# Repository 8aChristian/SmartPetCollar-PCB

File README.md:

# 🐾 SmartPet — Collar Inteligente para Mascotas (Smart Pet Collar PCB)

**SmartPet** es una solución de hardware embebido de grado industrial para collares inteligentes de mascotas (*pet wearables*). Diseñado en **KiCad 10**, integra procesamiento ultrarrápido con conectividad **Wi-Fi / Bluetooth Low Energy (BLE)**, posicionamiento satelital **GNSS/GPS con antena de parche integrada**, sensores de **actividad e inclinación triaxial (IMU)**, medición de **temperatura corporal (NTC)** y un sistema completo de **gestión de batería LiPo con recarga USB-C**.

---

## 📸 Vistas del Diseño de PCB

A continuación se presentan las vistas vectoriales de alta resolución del circuito impreso de 2 capas:

| Cara Superior (F.Cu & Serigrafía) | Cara Inferior (B.Cu & Ruteo 45°) |
| :---: | :---: |
|  |  |
| **Top Layer:** ESP32-C3, Módulo GPS, Cargador LiPo, IMU y Conectores | **Bottom Layer:** Sensor NTC, Pistas de Cruce y Plano GND de Retorno |

> 📄 **Documentación Gráfica y Planos de Fabricación:**
> - 🗺️ **Diagrama Esquemático Vectorial (SVG):** [`docs/SmartPet.svg`](docs/SmartPet.svg)
> - 📑 **Layout de PCB con Capas Combinadas (PDF):** [`docs/SmartPet_PCB_Layout.pdf`](docs/SmartPet_PCB_Layout.pdf)
> - 📦 **Paquete Completo de Gerbers RS-274X y Taladros Excellon:** [`fabrication/gerbers/`](fabrication/gerbers/)
> - 📐 **Reglas de Diseño Customizadas para Autorouter:** [`SmartPet.kicad_dru`](SmartPet.kicad_dru)

---

## ⚙️ Clases de Red y Reglas de Ruteo (NetClasses & Autorouter Rules)

El proyecto cuenta con **NetClasses jerárquicas preconfiguradas** según las normas **IPC-2152** e **IPC-2221** para garantizar un ruteo manual o automatizado (*Autorouter / Freerouting*) óptimo:

| Clase de Red (*NetClass*) | Redes Asignadas (*Nets*) | Ancho de Pista (*Width*) | Aislamiento (*Clearance*) | Vía (Diámetro / Taladro) | Función de Ingeniería |
| :--- | :--- | :--- | :--- | :--- | :--- |
| **`Power_Heavy`** | `VBUS`, `VBAT`, `GND` | **$0.80	ext{ mm}$** ($32	ext{ mil}$) | $0.35	ext{ mm}$ ($14	ext{ mil}$) | $arnothing 1.00	ext{ mm}$ / $0.50	ext{ mm}$ | Potencia principal de batería LiPo y bus USB-C (hasta 1.5A) |
| **`Power_Secondary`** | `+3.3V` | **$0.50	ext{ mm}$** ($20	ext{ mil}$) | $0.30	ext{ mm}$ ($12	ext{ mil}$) | $arnothing 0.80	ext{ mm}$ / $0.40	ext{ mm}$ | Riel regulado por LDO AP2112K para ESP32-C3 y sensores |
| **`Signals_Analog`** | `NTC_ADC`, `*ADC*` | **$0.35	ext{ mm}$** ($14	ext{ mil}$) | $0.25	ext{ mm}$ ($10	ext{ mil}$) | $arnothing 0.80	ext{ mm}$ / $0.40	ext{ mm}$ | Señal analógica de temperatura con filtro RC |
| **`Default` / `Digital`** | `I2C_*`, `GPS_*`, `ESP_*`, `USB_*`, `LED_*`, `LIS3DH_*` | **$0.25	ext{ mm}$** ($10	ext{ mil}$) | $0.20	ext{ mm}$ ($8	ext{ mil}$) | $arnothing 0.80	ext{ mm}$ / $0.40	ext{ mm}$ | Buses digitales de alta y media velocidad (I2C, UART, GPIOs) |

---

## 1. 🏗️ Arquitectura General del Sistema

```mermaid
graph TD
    subgraph ALIMENTACIÓN & GESTIÓN DE ENERGÍA
        USBC[Puerto USB-C 16P] -->|VBUS 5.0V| CHG[MCP73831T Cargador LiPo 4.2V]
        BATT[Batería LiPo 3.7V 350mAh] <-->|VBAT| CHG
        CHG -->|VBAT| LDO[AP2112K-3.3 CMOS Ultra-LDO 600mA]
        LDO -->|+3.3V Power Rail| VCC_BUS[Rail de Potencia 3.3V Limpio]
    end

    subgraph PROCESAMIENTO & COMUNICACIONES
        VCC_BUS --> MCU[ESP32-C3-WROOM-02-N4<br/>RISC-V 32-bit @ 160MHz]
        MCU -->|BLE Beacon 2.4GHz| BLE_PING[Rastreo Local Proximidad AirTag]
        MCU -->|Wi-Fi 802.11 b/g/n| CLOUD[Sincronización en el Hogar]
    end

    subgraph LOCALIZACIÓN SATELITAL
        VCC_BUS --> GPS[u-blox SAM-M8Q GNSS<br/>Antena de Parche Integrada]
        GPS -->|UART NMEA TX/RX @ 9600-115200| MCU
        GPS -->|Bus I2C DDC| MCU
    end

    subgraph SENSORES BIOMÉTRICOS & ACTIVIDAD
        VCC_BUS --> IMU[LIS3DH Acelerómetro Triaxial LGA-16]
        IMU -->|Bus I2C + INT1/INT2| MCU
        VCC_BUS --> NTC_DIV[Divisor de Tensión NTC 10k 1%]
        NTC_DIV -->|Canal SAR ADC| MCU
    end

    subgraph INTERFAZ DE USUARIO
        MCU -->|GPIO LED_STAT| D2[LED Azul de Estado 0603]
        CHG -->|Pin STAT| D1[LED Rojo de Carga 0603]
        SW1[Pulsador RESET SMD] -->|Línea EN| MCU
        SW2[Pulsador BOOT SMD] -->|Línea IO9| MCU
    end
```

---

## 2. 📋 Selección de Componentes y Justificación Técnica

| Subsistema | Componente | Encapsulado | Función y Justificación de Ingeniería |
| :--- | :--- | :--- | :--- |
| **Cerebro / Conectividad** | **ESP32-C3-WROOM-02-N4** | SMD Module (18x20mm) | SoC RISC-V de 32 bits a 160 MHz con Wi-Fi 4 y Bluetooth 5 (LE). Emite beacons de proximidad (*tipo AirTag*) con consumo en reposo inferior a $5\,\mu	ext{A}$ (*Deep Sleep*). |
| **Receptor GNSS/GPS** | **u-blox SAM-M8Q** | 15.5 x 15.5 mm | Módulo GPS/GLONASS/Galileo miniatura con **antena de parche cerámica integrada de fábrica**. Ahorra más del 70% de espacio en PCB y suprime la necesidad de líneas microstrip de 50Ω. |
| **Sensor de Movimiento** | **LIS3DH** | LGA-16 (3x3 mm) | Acelerómetro triaxial de ultra-bajo consumo ($2\,\mu	ext{A}$ en modo low-power) para monitoreo de actividad física, sueño y detección de caídas con interrupción por umbral. |
| **Temperatura Corporal** | **NTC 10k 1% (TH1)** | SMD 0603 | Termistor de precisión acoplado a un divisor resistivo con filtro RC ($10	ext{ nF}$) conectado al canal SAR ADC interno del ESP32-C3. |
| **Gestión de Carga** | **MCP73831T-2ACI/OT** | SOT-23-5 | Cargador lineal LiPo monocelda (4.2V), configurado a corriente de carga $I_{CHG} = 300	ext{ mA}$ mediante $R_{PROG} = 3.3	ext{ k}\Omega$. |
| **Regulación LDO** | **AP2112K-3.3TRG1** | SOT-23-5 | Regulador LDO CMOS de 600mA con caída ultra-baja ($V_{drop} pprox 250	ext{ mV}$ a 600mA), garantizando estabilidad frente a los picos de RF del Wi-Fi. |
| **Conector de Recarga** | **USB-C 16-pin (GCT USB4105)** | SMD Top-Mount | Puerto de recarga universal con resistencias pulldown de $5.1	ext{ k}\Omega$ en pines CC1 y CC2 según estándar USB Type-C Power Delivery. |
| **Conector de Batería** | **JST-SH 1.0mm 2-pin** | SMD Horizontal | Conector ultracompacto con bloqueo para celda de polímero de litio 1S (3.7V, 300–400 mAh). |

---

## 3. ⚡ Topología de Potencia y Supresión de Ruido

1. **Desacoplo en Trayectoria Directa**:
   - Cada circuito integrado cuenta con condensadores de desacoplo ($C_{IN}, C_{OUT}$) ubicados directamente en la entrada de sus pines de alimentación antes de cualquier bifurcación.
2. **Filtrado Analógico del ADC**:
   - El nodo de lectura del divisor NTC incorpora un filtro paso bajo pasivo ($R = 10	ext{ k}\Omega, C = 10	ext{ nF}, f_c pprox 1.59	ext{ kHz}$) para inmunidad contra el ruido de conmutación digital.
3. **Plano de Tierra Analógico/Digital Unificado**:
   - Ambos lados de la placa (F.Cu y B.Cu) están cubiertos por un plano de tierra GND continuo con conexiones térmicas (*thermal reliefs*).

---

## 4. 📐 Reglas de Ruteo y Normas DFM (IPC-2152)

- **Prohibición Estricta de Ángulos de 90°**: Todas las pistas utilizan biseles a **45° (*45-degree mitered chamfering*)** o arcos suaves para prevenir trampas de ácido (*acid traps*) y saltos capacitivos.
- **Despeje al Borde de la Placa (*Edge Pullback*)**: Mínimo de $\ge 1.0	ext{ mm}$ entre cualquier elemento de cobre y el contorno exterior `Edge_Cuts`.
- **Zona de Exclusión de Antena (*RF Keepout Area*)**:
  - El área superior de la antena de traza del ESP32-C3 ($Y < 56.5	ext{ mm}$) se mantiene **100% libre de pistas y planos de cobre** en ambas capas para maximizar el alcance de RF.

---

## 5. 📦 Lista de Materiales (Bill of Materials - BOM)

| Ref Des | Cantidad | Valor / Descripción | Encapsulado | Fabricante / MPN Sugerido |
| :--- | :---: | :--- | :--- | :--- |
| **U1** | 1 | ESP32-C3-WROOM-02-N4 (RISC-V BLE/WiFi) | Module SMD | Espressif ESP32-C3-WROOM-02-N4 |
| **U2** | 1 | MCP73831T-2ACI/OT (LiPo Charger 4.2V) | SOT-23-5 | Microchip MCP73831T-2ACI/OT |
| **U3** | 1 | AP2112K-3.3TRG1 (LDO 3.3V 600mA) | SOT-23-5 | Diodes Inc. AP2112K-3.3TRG1 |
| **U4** | 1 | LIS3DH (Acelerómetro Triaxial I2C/SPI) | LGA-16 (3x3mm) | STMicroelectronics LIS3DHTR |
| **U5** | 1 | SAM-M8Q (Receptor GNSS con Antena) | 15.5x15.5mm | u-blox SAM-M8Q-0-10 |
| **J1** | 1 | Conector Batería LiPo 1S 1.0mm | JST-SH 2P SMD | JST SM02B-SRSS-TB |
| **J2** | 1 | Conector USB-C 16-Pines Power Only | Top-Mount SMD | GCT USB4105-GF-A |
| **SW1, SW2** | 2 | Pulsador Táctil SMD (Reset / Boot) | 4-Pin SMD | E-Switch TL3342F160QG |
| **D1** | 1 | LED SMD Rojo (Indicador de Carga) | 0603 Metric | Lite-On LTST-C190KRKT |
| **D2** | 1 | LED SMD Azul (Estado / BLE) | 0603 Metric | Lite-On LTST-C190TBKT |
| **TH1** | 1 | Termistor NTC 10k 1% B=3950K | 0603 Metric | Murata NCP18XH103F03RB |
| **R1** | 1 | 3.3kΩ 1% (R_PROG 300mA) | 0603 Metric | Yageo RC0603FR-073K3L |
| **R2, R11** | 2 | 1.0kΩ 5% (LED Resistors) | 0603 Metric | Yageo RC0603JR-071KL |
| **R3, R4** | 2 | 5.1kΩ 1% (USB-C CC1/CC2 Pulldown) | 0603 Metric | Yageo RC0603FR-075K1L |
| **R5, R6** | 2 | 10kΩ 5% (Pullups EN / Boot) | 0603 Metric | Yageo RC0603JR-0710KL |
| **R7, R8** | 2 | 4.7kΩ 1% (Pullups Bus I2C) | 0603 Metric | Yageo RC0603FR-074K7L |
| **R9** | 1 | 10kΩ 0.1% / 1% (Divisor NTC) | 0603 Metric | Yageo RC0603FR-0710KL |
| **C1, C2, C3**| 3 | 4.7μF 10V X5R/X7R Ceramic | 0603 Metric | Murata GRM188R61A475KE15D |
| **C4, C5, C7, C8** | 4 | 0.1μF 16V X7R Ceramic | 0603 Metric | Murata GRM188R71C104KA01D |
| **C6** | 1 | 10nF 25V X7R Ceramic (Filtro NTC) | 0603 Metric | Murata GRM188R71E103KA01D |

---

## 6. 🦮 Guía Mecánica y Diseño del Case / Gabinete (IP67)

Para garantizar la durabilidad y precisión de las lecturas en una mascota:

1. **Orientación de la Antena GPS (U5)**:
   - La cara superior del módulo GPS debe apuntar **hacia el cielo** (hacia el exterior del collar). El material de la carcasa superior debe ser de plástico dieléctrico homogéneo (ABS, PETG, TPU o Policarbonato) **sin partes metálicas ni baterías sobre el módulo**.
2. **Acoplamiento Térmico del Termistor (TH1)**:
   - TH1 está ubicado en la cara inferior de la PCB. La carcasa debe contar con un **remache o contacto metálico de acero inoxidable** con silicona conductora térmica en contacto con el pelaje/piel de la mascota para medir la temperatura real del animal.
3. **Resistencia al Agua (IP67)**:
   - Utilizar una junta de goma/silicona (*O-ring*) en el cierre perimetral de la caja con 4 tornillos de acero inoxidable M2.
   - El puerto USB-C (J2) debe protegerse con una **tapa hermética de silicona** cautiva en la carcasa.
4. **Guías de Luz (*Light Pipes*)**:
   - Usar cilindros de policarbonato translúcido para canalizar los LEDs D1 y D2 hacia la superficie del case sin abrir orificios de entrada de agua.

---

## 7. 🚀 Instrucciones de Fabricación y Apertura

### Apertura en KiCad 10
1. Clonar el repositorio:
   ```bash
   git clone https://github.com/8aChristian/SmartPetCollar-PCB.git
   ```
2. Abrir el archivo `SmartPet.kicad_pro` en **KiCad 10.0+**.
3. Presionar `Alt + 3` para abrir el Visor 3D nativo.

### Fabricación Industrial (JLCPCB / PCBWay)
1. Los archivos Gerber listos para producción se encuentran en [`fabrication/gerbers/`](fabrication/gerbers/).
2. Comprimir el contenido de la carpeta `fabrication/gerbers/` en un archivo `.zip` y cargarlo en la plataforma de manufactura.

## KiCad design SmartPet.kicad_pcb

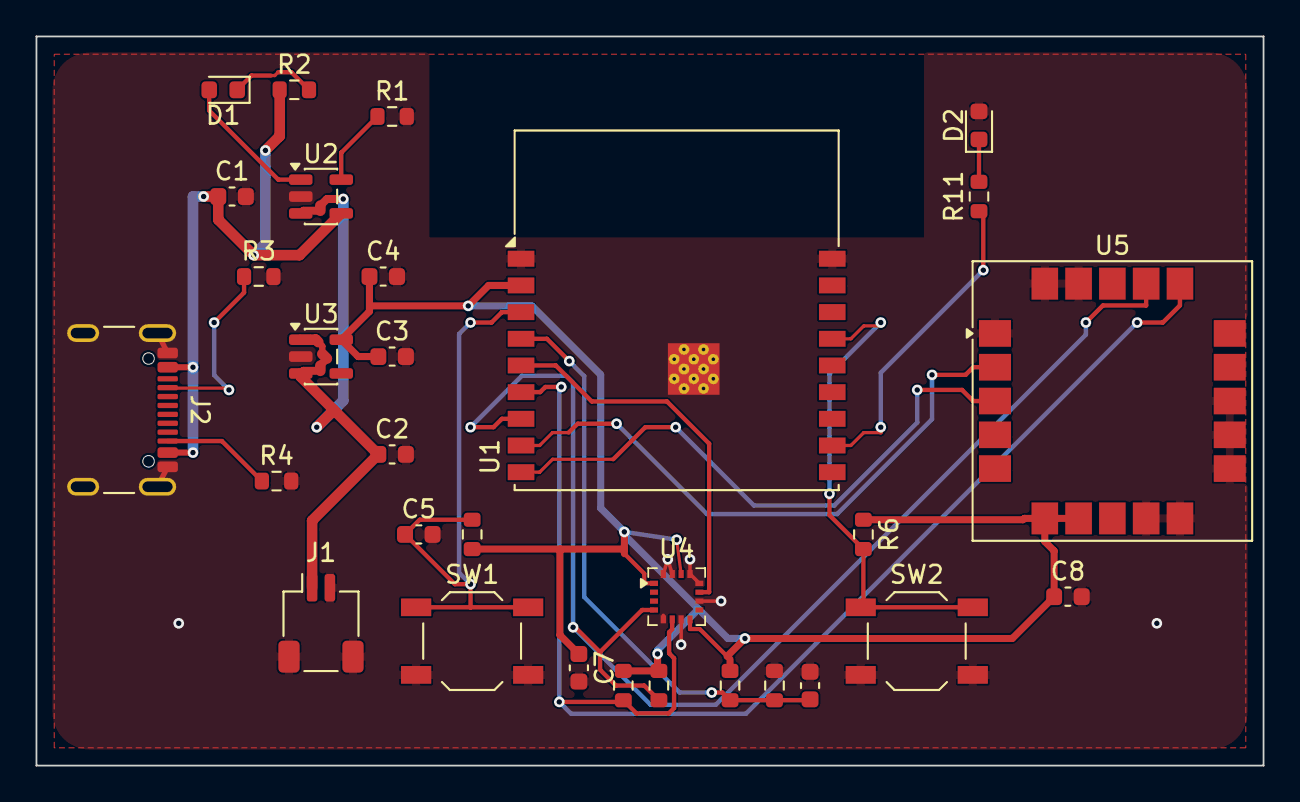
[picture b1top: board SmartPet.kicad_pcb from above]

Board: 2 copper layers, 69.0 x 41.0 mm, 30 parts (0 on the bottom side), 19 nets.

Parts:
C1, C2, C3: 4.7uF; C_0603_1608Metric
C4, C5, C7, C8: 0.1uF; C_0603_1608Metric
C6: 10nF; C_0603_1608Metric
D1: RED; LED_0603_1608Metric
D2: BLUE; LED_0603_1608Metric
J1: BATT_1S; JST_SH_SM02B-SRSS-TB_1x02-1MP_P1.00mm_Horizontal
J2: USB-C; USB_C_Receptacle_GCT_USB4105-xx-A_16P_TopMnt_Horizontal
R1: 3.3k; R_0603_1608Metric
R2, R11: 1k; R_0603_1608Metric
R3, R4: 5.1k; R_0603_1608Metric
R5, R6: 10k; R_0603_1608Metric
R7, R8: 4.7k; R_0603_1608Metric
R9: 10k 1%; R_0603_1608Metric
SW1: RESET; SW_SPST_TL3342
SW2: BOOT; SW_SPST_TL3342
TH1: 10k NTC; R_0603_1608Metric
U1: ESP32-C3-WROOM-02-N4; ESP32-C3-WROOM-02
U2: MCP73831T-2ACI/OT; SOT-23-5
U3: AP2112K-3.3TRG1; SOT-23-5
U4: LIS3DH; LGA-16_3x3mm_P0.5mm
U5: SAM-M8Q; ublox_SAM-M8Q

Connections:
+3.3V: C3.1, C4.1, C7.1, C8.1, R5.1, R6.1, R7.1, R8.1, R9.1, U1.2, U3.5, U4.1, U4.8, U4.14, U5.6, U5.7
CHG_LED_A: D1.1, R2.2
CHG_STAT: D1.2, U2.1
ESP_BOOT: R6.2, SW2.1, U1.15
ESP_EN: C5.1, R5.2, SW1.1, U1.3
GND: C1.2, C2.2, C3.2, C4.2, C5.2, C6.2, C7.2, C8.2, D2.2, J1.2, J1.MP, J2.A1, J2.A12, J2.B1, J2.B12, J2.SH, R1.2, R3.2, R4.2, SW1.2, SW2.2, TH1.2, U1.1, U1.18, U1.19, U2.2, U3.2, U4.5, U4.7, U4.10, U4.12, U4.13, U4.15, U4.16, U5.1, U5.9, U5.10, U5.11, U5.12, U5.13, U5.19, U5.20
GPS_RX: U1.9, U5.3
GPS_TX: U1.8, U5.2
I2C_SCL: R8.2, U1.7, U4.4, U5.17
I2C_SDA: R7.2, U1.6, U4.6, U5.16
LED_STAT: R11.1, U1.11
LED_STAT_A: D2.1, R11.2
LIS3DH_INT: U1.5, U4.11
MCP_PROG: R1.1, U2.5
NTC_ADC: C6.1, R9.2, TH1.1, U1.4
USB_CC1: J2.A5, R3.1
USB_CC2: J2.B5, R4.1
VBAT: C2.1, J1.1, U2.3, U3.1, U3.3
VBUS: C1.1, J2.A4, J2.A9, J2.B4, J2.B9, R2.1, U2.4

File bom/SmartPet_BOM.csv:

Reference,Value,Footprint,Description,Manufacturer,MPN,Qty
U1,ESP32-C3-WROOM-02-N4,RF_Module:ESP32-C3-WROOM-02,"MCU Wi-Fi 4 + BLE 5.0 SoC RISC-V 160MHz 4MB Flash",Espressif,ESP32-C3-WROOM-02-N4,1
U2,MCP73831T-2ACI/OT,Package_TO_SOT_SMD:SOT-23-5,"IC Li-Ion/Li-Po Charge Controller CC/CV 4.2V 500mA",Microchip,MCP73831T-2ACI/OT,1
U3,AP2112K-3.3TRG1,Package_TO_SOT_SMD:SOT-23-5,"IC LDO Regulator 3.3V 600mA Low Dropout SOT-23-5",Diodes Incorporated,AP2112K-3.3TRG1,1
U4,LIS3DH,Package_LGA:LGA-16_3x3mm_P0.5mm,"Ultra Low Power 3-Axis Accelerometer I2C/SPI LGA-16",STMicroelectronics,LIS3DH,1
U5,SAM-M8Q,RF_GPS:ublox_SAM-M8Q,"Miniature Concurrent GNSS Module with Integrated Patch Antenna",u-blox,SAM-M8Q-0-10,1
J1,BATT_1S_3.7V,Connector_JST:JST_SH_SM02B-SRSS-TB_1x02-1MP_P1.00mm_Horizontal,"2-Pin 1.00mm Pitch JST-SH Connector for LiPo Battery",JST,SM02B-SRSS-TB,1
J2,USB-C_POWER,Connector_USB:USB_C_Receptacle_GCT_USB4105-xx-A_16P_TopMnt_Horizontal,"USB Type-C 16-Pin Power Receptacle SMD",GCT,USB4105-GF-A,1
SW1,RESET,Button_Switch_SMD:SW_SPST_TL3342,"Push Button Tactile SPST SMD 4-Pin",E-Switch,TL3342F160QG,1
SW2,BOOT_USER,Button_Switch_SMD:SW_SPST_TL3342,"Push Button Tactile SPST SMD 4-Pin",E-Switch,TL3342F160QG,1
D1,RED (CHG),LED_SMD:LED_0603_1608Metric,"LED Red 0603 SMD Charge Status",Everlight,19-217-R6C-AL1M2VY-3T,1
D2,BLUE (STATUS),LED_SMD:LED_0603_1608Metric,"LED Blue 0603 SMD System/BLE Status",Everlight,19-217-BHC-ZL1M2RY-3T,1
TH1,10k NTC,Resistor_SMD:R_0603_1608Metric,"Thermistor NTC 10k 5% 0603",Murata,NCP18XH103J03RB,1
R1,3.3k,Resistor_SMD:R_0603_1608Metric,"Resistor 3.3k 1% 1/10W 0603 (Charge Current 300mA)",Yageo,RC0603FR-073K3L,1
R2,1k,Resistor_SMD:R_0603_1608Metric,"Resistor 1k 5% 1/10W 0603 (CHG LED Limit)",Yageo,RC0603JR-071KL,1
R3,5.1k,Resistor_SMD:R_0603_1608Metric,"Resistor 5.1k 1% 1/10W 0603 (USB CC1 Pulldown)",Yageo,RC0603FR-075K1L,1
R4,5.1k,Resistor_SMD:R_0603_1608Metric,"Resistor 5.1k 1% 1/10W 0603 (USB CC2 Pulldown)",Yageo,RC0603FR-075K1L,1
R5,10k,Resistor_SMD:R_0603_1608Metric,"Resistor 10k 5% 1/10W 0603 (EN Pull-up)",Yageo,RC0603JR-0710KL,1
R6,10k,Resistor_SMD:R_0603_1608Metric,"Resistor 10k 5% 1/10W 0603 (Boot Pull-up)",Yageo,RC0603JR-0710KL,1
R7,4.7k,Resistor_SMD:R_0603_1608Metric,"Resistor 4.7k 5% 1/10W 0603 (I2C SDA Pull-up)",Yageo,RC0603JR-074K7L,1
R8,4.7k,Resistor_SMD:R_0603_1608Metric,"Resistor 4.7k 5% 1/10W 0603 (I2C SCL Pull-up)",Yageo,RC0603JR-074K7L,1
R9,10k 1%,Resistor_SMD:R_0603_1608Metric,"Resistor 10k 1% 1/10W 0603 (NTC Voltage Divider)",Yageo,RC0603FR-0710KL,1
R11,1k,Resistor_SMD:R_0603_1608Metric,"Resistor 1k 5% 1/10W 0603 (STATUS LED Limit)",Yageo,RC0603JR-071KL,1
C1,4.7uF 10V,Capacitor_SMD:C_0603_1608Metric,"Capacitor Ceramic 4.7uF 10V X5R 0603 (VBUS Filter)",Murata,GRM188R61A475KE15D,1
C2,4.7uF 10V,Capacitor_SMD:C_0603_1608Metric,"Capacitor Ceramic 4.7uF 10V X5R 0603 (VBAT Filter)",Murata,GRM188R61A475KE15D,1
C3,4.7uF 6.3V,Capacitor_SMD:C_0603_1608Metric,"Capacitor Ceramic 4.7uF 6.3V X5R 0603 (3.3V Output)",Murata,GRM188R60J475KE19D,1
C4,0.1uF 16V,Capacitor_SMD:C_0603_1608Metric,"Capacitor Ceramic 0.1uF 16V X7R 0603 (3.3V HF Bypass)",Murata,GRM188R71C104KA01D,1
C5,0.1uF 16V,Capacitor_SMD:C_0603_1608Metric,"Capacitor Ceramic 0.1uF 16V X7R 0603 (Reset Timing)",Murata,GRM188R71C104KA01D,1
C6,10nF 25V,Capacitor_SMD:C_0603_1608Metric,"Capacitor Ceramic 10nF 25V X7R 0603 (NTC ADC Filter)",Murata,GRM188R71E103KA01D,1
C7,0.1uF 16V,Capacitor_SMD:C_0603_1608Metric,"Capacitor Ceramic 0.1uF 16V X7R 0603 (LIS3DH Decoupling)",Murata,GRM188R71C104KA01D,1
C8,0.1uF 16V,Capacitor_SMD:C_0603_1608Metric,"Capacitor Ceramic 0.1uF 16V X7R 0603 (GPS Decoupling)",Murata,GRM188R71C104KA01D,1

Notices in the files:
README.md:
License: MIT
